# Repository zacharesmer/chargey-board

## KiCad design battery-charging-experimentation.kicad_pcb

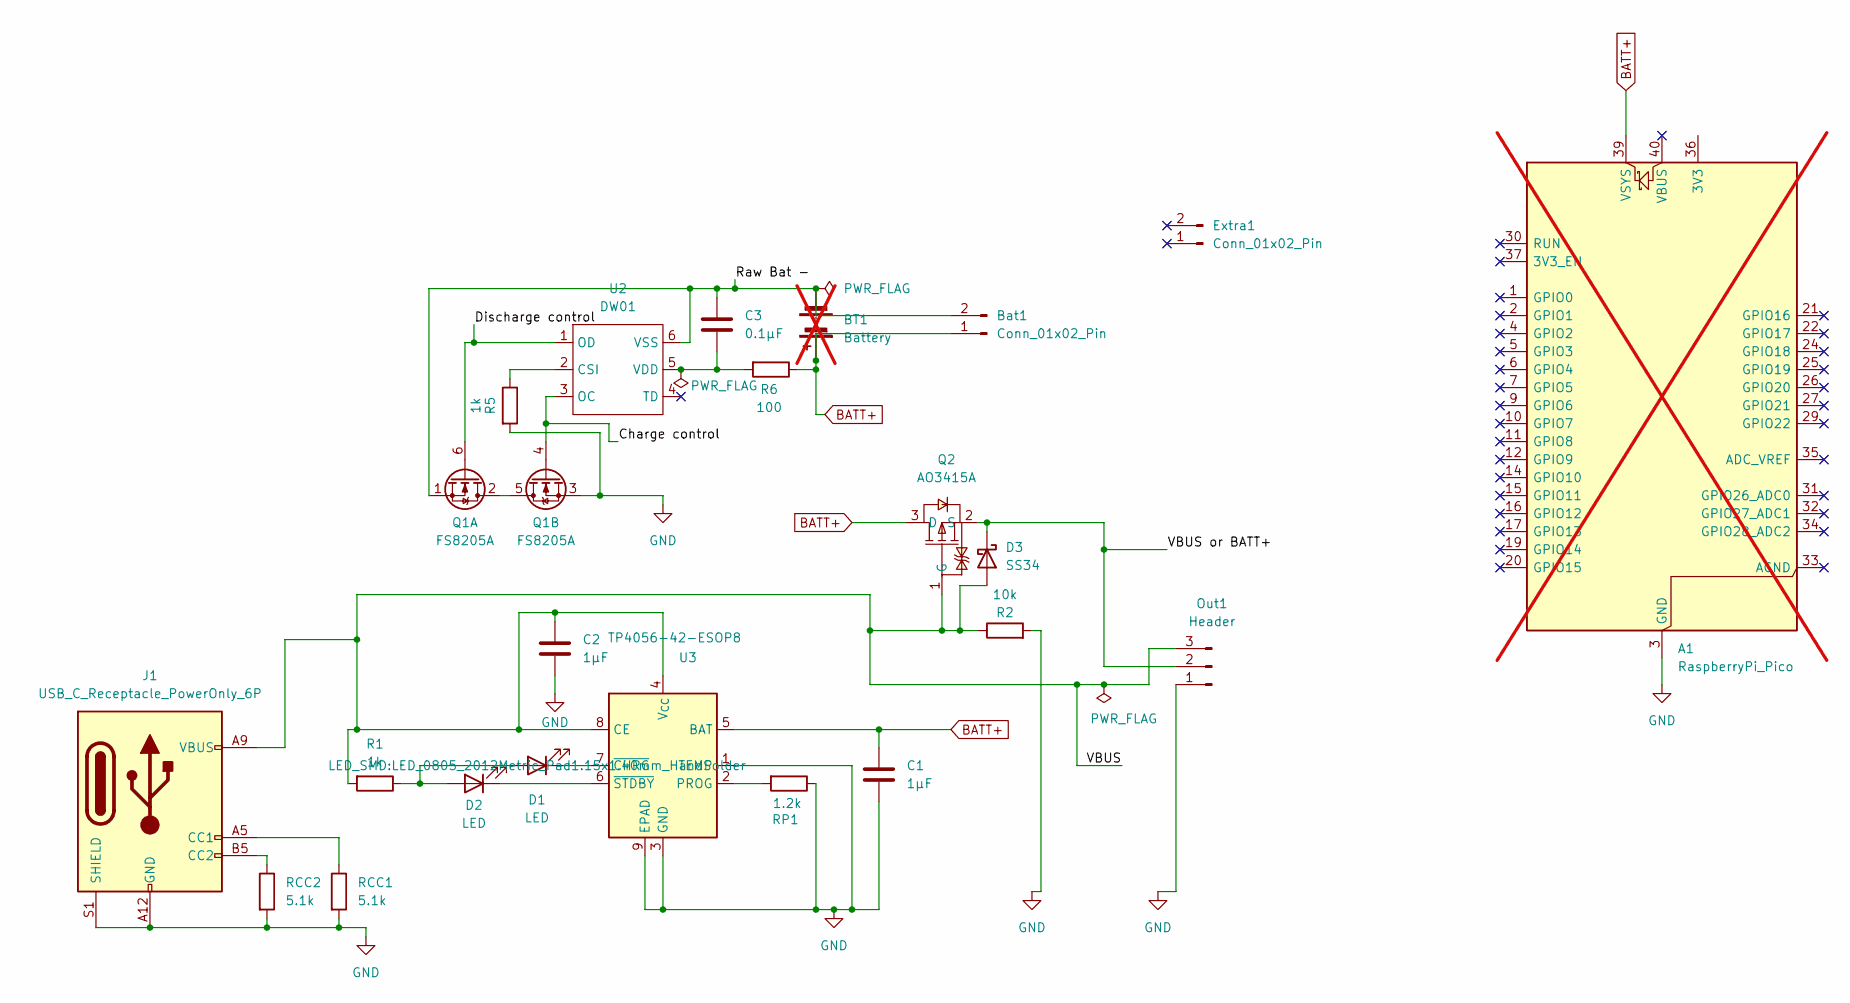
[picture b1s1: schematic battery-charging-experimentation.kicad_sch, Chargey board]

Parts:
A1: RaspberryPi_Pico; RaspberryPi_Pico_Common_Unspecified; not fitted
BT1: Battery; BatteryHolder_MPD_BH-18650-PC; not fitted
Bat1: Conn_01x02_Pin; PinHeader_1x02_P2.54mm_Vertical
C1, C2: 1μF; C_0402_1005Metric_Pad0.74x0.62mm_HandSolder; LCSC Part C52923
C3: 0.1μF; C_0402_1005Metric_Pad0.74x0.62mm_HandSolder; LCSC Part C1525
D1: LED; LED_0805_2012Metric_Pad1.15x1.40mm_HandSolder; LCSC Part C2296
D2: LED; LED_0805_2012Metric_Pad1.15x1.40mm_HandSolder; LCSC Part C2297
D3: SS34; SMA_L4.3-W2.6-LS5.2-RD; LCSC Part C8678
Extra1: Conn_01x02_Pin; PinHeader_1x02_P2.54mm_Vertical
J1: USB_C_Receptacle_PowerOnly_6P; USB-C-SMD; LCSC Part C7507406
Out1: Header; PinHeader_1x03_P2.54mm_Vertical; LCSC Part C52016390
Q1: FS8205A; SOT-23-6; LCSC Part C2830320
Q2: AO3415A; SOT-23-3_L2.9-W1.6-P1.90-LS2.8-BR; LCSC Part C5350990
R1, R5: 1k; R_0402_1005Metric_Pad0.72x0.64mm_HandSolder; LCSC Part C11702
R2: 10k; R_0402_1005Metric_Pad0.72x0.64mm_HandSolder; LCSC Part C25744
R6: 100; R_0402_1005Metric_Pad0.72x0.64mm_HandSolder; LCSC Part C25076
RCC1, RCC2: 5.1k; R_0402_1005Metric_Pad0.72x0.64mm_HandSolder; LCSC Part C25905
RP1: 1.2k; R_0402_1005Metric_Pad0.72x0.64mm_HandSolder; LCSC Part C25862
U2: DW01; SOT-23-6; LCSC Part C917079
U3: TP4056-42-ESOP8; SOIC-8-1EP_3.9x4.9mm_P1.27mm_EP2.41x3.3mm_ThermalVias; LCSC Part C382139

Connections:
/Charge control: Q1.4 (G), U2.3 (OC)
/Discharge control: Q1.6 (G), U2.1 (OD)
/Raw Bat -: BT1.2 (-), Bat1.2, C3.1, Q1.1 (D), U2.6 (VSS)
/VBUS: C2.1, D3.2 (A), J1.A9 (VBUS), J1.B9 (VBUS), Out1.3, Q2.1 (G), R1.2, R2.1, U3.4 (V_{CC}), U3.8 (CE)
/VBUS or BATT+: D3.1 (K), Out1.2, Q2.2 (S)
BATT+: A1.39 (VSYS), BT1.1 (+), Bat1.1, C1.1, Q2.3 (D), R6.1, U3.5 (BAT)
GND: A1.3 (GND), A1.8 (GND), A1.13 (GND), A1.18 (GND), A1.23 (GND), A1.28 (GND), A1.38 (GND), C1.2, C2.2, J1.A12 (GND), J1.B12 (GND), J1.S1 (SHIELD), Out1.1, Q1.3 (D), R2.2, R5.2, RCC1.2, RCC2.2, RP1.1, U3.1 (TEMP), U3.3 (GND), U3.9 (EPAD)
unnamed: D1.2 (A), D2.2 (A), R1.1
unnamed: D1.1 (K), U3.7 (~CHRG)
unnamed: D2.1 (K), U3.6 (~STDBY)
unnamed: J1.A5 (CC1), RCC1.1
unnamed: J1.B5 (CC2), RCC2.1
unnamed: Q1.2 (S), Q1.5 (S)
unnamed: R5.1, U2.2 (CSI)
unnamed: C3.2, R6.2, U2.5 (VDD)
unnamed: RP1.2, U3.2 (PROG)

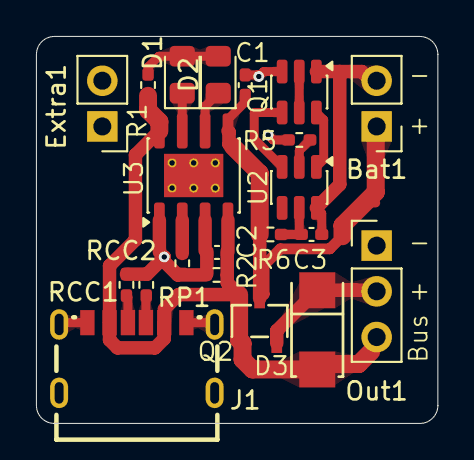
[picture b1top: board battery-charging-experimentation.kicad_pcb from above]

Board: 2 copper layers, 22.3 x 21.5 mm, 21 parts (0 on the bottom side), 16 nets.

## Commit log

2026-02-04 move diode so the thing actually works
2026-02-04 add a vbus out pin
2026-02-05 smaller components, power from pico USB port
2026-02-05 put the usb port on smol version
2026-02-05 update lcsc parts (double check before ordering though)
2026-02-05 minor adjustments
2026-02-05 lord knows what this is
2026-02-05 use LEDs that actually exist
2026-02-05 add switch to turn off pico
2026-02-05 update lcsc parts
2026-02-05 update bom and clean up silkscreen
